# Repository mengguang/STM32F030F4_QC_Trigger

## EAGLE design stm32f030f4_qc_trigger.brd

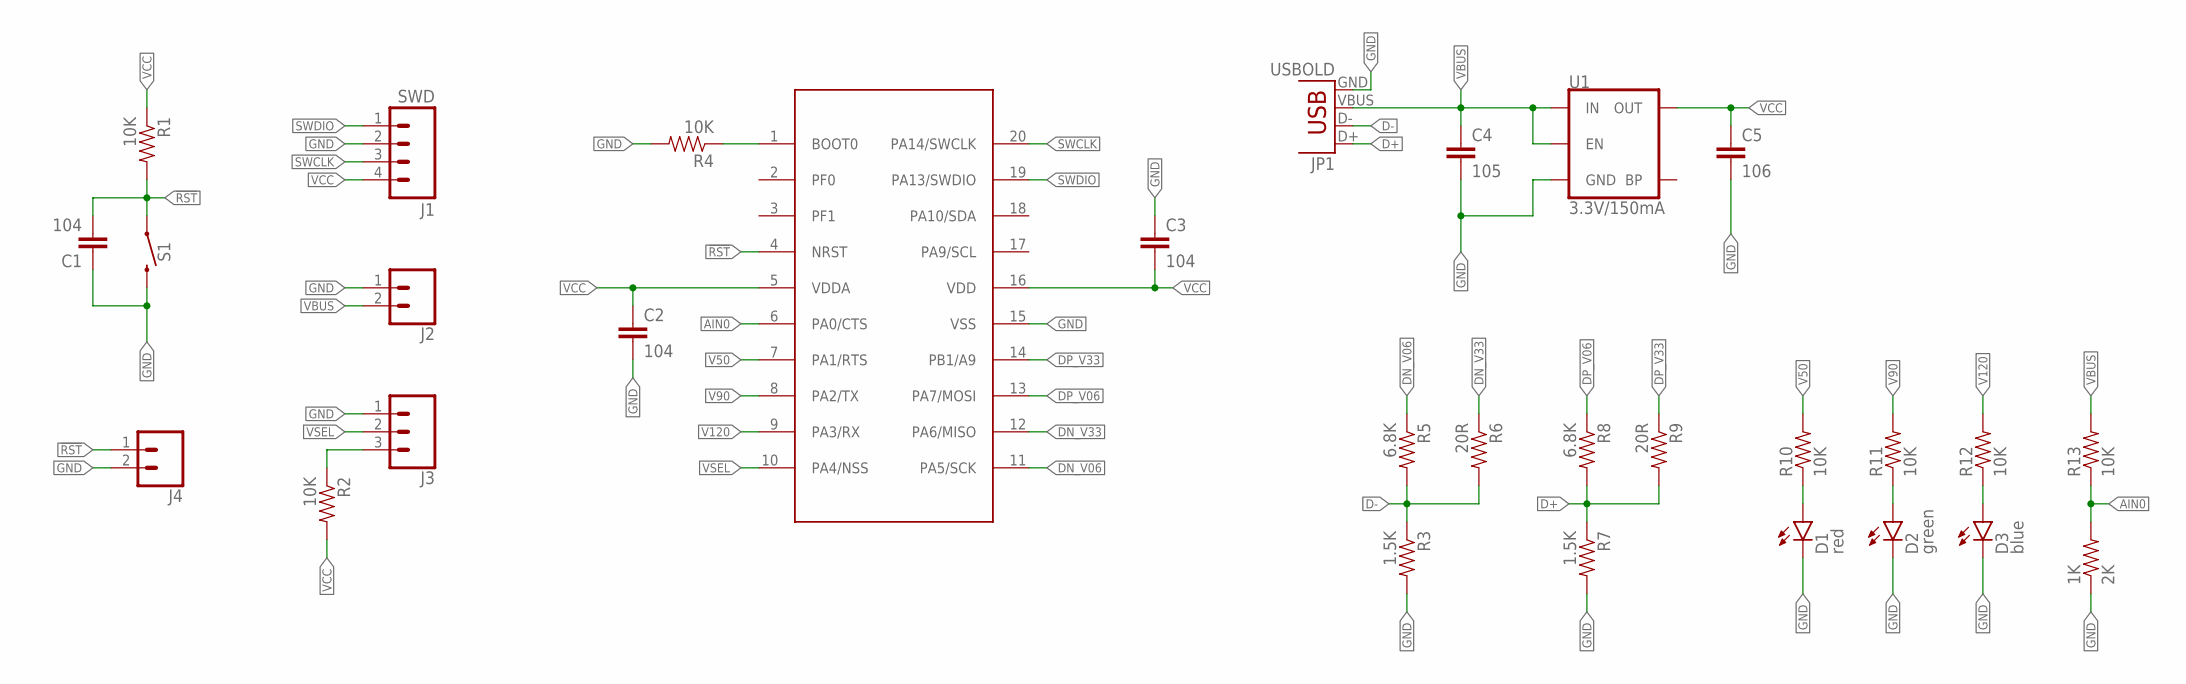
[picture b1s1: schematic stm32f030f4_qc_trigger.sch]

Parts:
1K: 2K; 0402-RES
C1, C2, C3: 104; 0402-CAP
C4: 105; 0603-CAP
C5: 106; 0402-CAP
D1: red; LED-0603-EASY
D2: green; LED-0603-EASY
D3: blue; LED-0603-EASY
J1: SWD; 1X04_NO_SILK
J2: CONN_025MM; SCREWTERMINAL-5MM-2
J3: CONN_031X03_NO_SILK; 1X03_NO_SILK
J4: CONN_021X02_NO_SILK; 1X02_NO_SILK
JP1: USBOLD; USB-MINIB-OLD
R1, R2, R4, R10, R11, R12, R13: 10K; 0402-RES
R3, R7: 1.5K; 0402-RES
R5, R8: 6.8K; 0402-RES
R6, R9: 20R; 0402-RES
S1: MOMENTARY-SWITCH-SPST-PTH-6.0MM; TACTILE_SWITCH_PTH_6.0MM
U1: 3.3V/150mA; SOT23-5
U2: STM32F030F4; TSSOP20

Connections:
!RST: C1.2, J4.1, R1.2, S1.1, U2.4 (NRST)
AIN0: 1K.2, R13.1, U2.6 (PA0/CTS)
D+: JP1.D+, R7.1, R8.2, R9.2
D-: JP1.D-, R3.1, R5.2, R6.2
DN_V06: R5.1, U2.11 (PA5/SCK)
DN_V33: R6.1, U2.12 (PA6/MISO)
DP_V06: R8.1, U2.13 (PA7/MOSI)
DP_V33: R9.1, U2.14 (PB1/A9)
GND: 1K.1, C1.1, C2.2, C3.1, C4.2, C5.2, D1.- (C), D2.- (C), D3.- (C), J1.2, J2.1, J3.1, J4.2, JP1.GND, R3.2, R4.2, R7.2, S1.3 (2), U1.2 (GND), U2.15 (VSS)
unnamed: J3.3, R2.1
unnamed: D1.+ (A), R10.1
unnamed: R4.1, U2.1 (BOOT0)
unnamed: D2.+ (A), R11.1
unnamed: D3.+ (A), R12.1
SWCLK: J1.3, U2.20 (PA14/SWCLK)
SWDIO: J1.1, U2.19 (PA13/SWDIO)
V50: R10.2, U2.7 (PA1/RTS)
V90: R11.2, U2.8 (PA2/TX)
V120: R12.2, U2.9 (PA3/RX)
VBUS: C4.1, J2.2, JP1.VBUS, R13.2, U1.1 (IN), U1.3 (EN)
VCC: C2.1, C3.2, C5.1, J1.4, R1.1, R2.2, U1.5 (OUT), U2.5 (VDDA), U2.16 (VDD)
VSEL: J3.2, U2.10 (PA4/NSS)

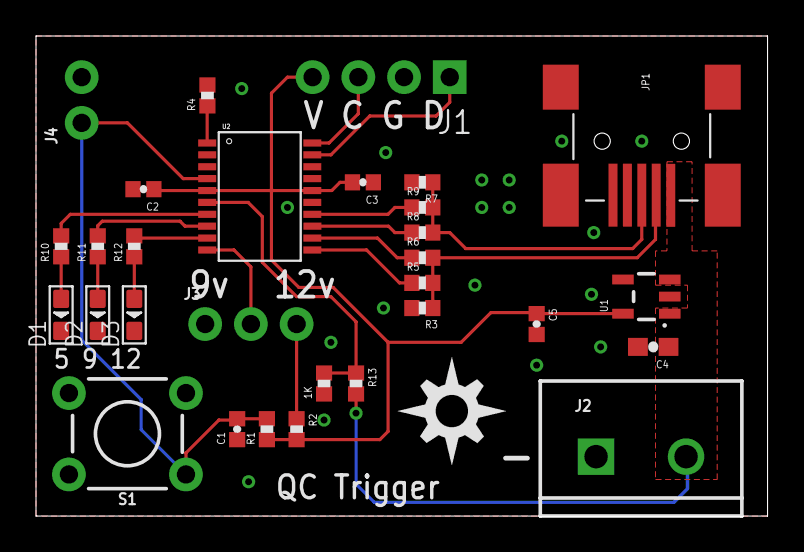
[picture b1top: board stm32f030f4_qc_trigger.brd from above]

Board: 2 copper layers, 40.6 x 26.7 mm, 31 parts (0 on the bottom side), 22 nets.

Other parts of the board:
U$1: DIYNOVA_LOGO

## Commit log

2020-06-30 import from old backup

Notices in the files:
parts and their libraries:
SparkFun-Connectors: Licensing: Creative Commons ShareAlike 4.0 International - https://creativecommons.org/licenses/by-sa/4.0
